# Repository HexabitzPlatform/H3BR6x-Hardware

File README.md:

# H3BR6x-Hardware
Hexabitz 6-Digit 7-Segment Display Module Hardware Design

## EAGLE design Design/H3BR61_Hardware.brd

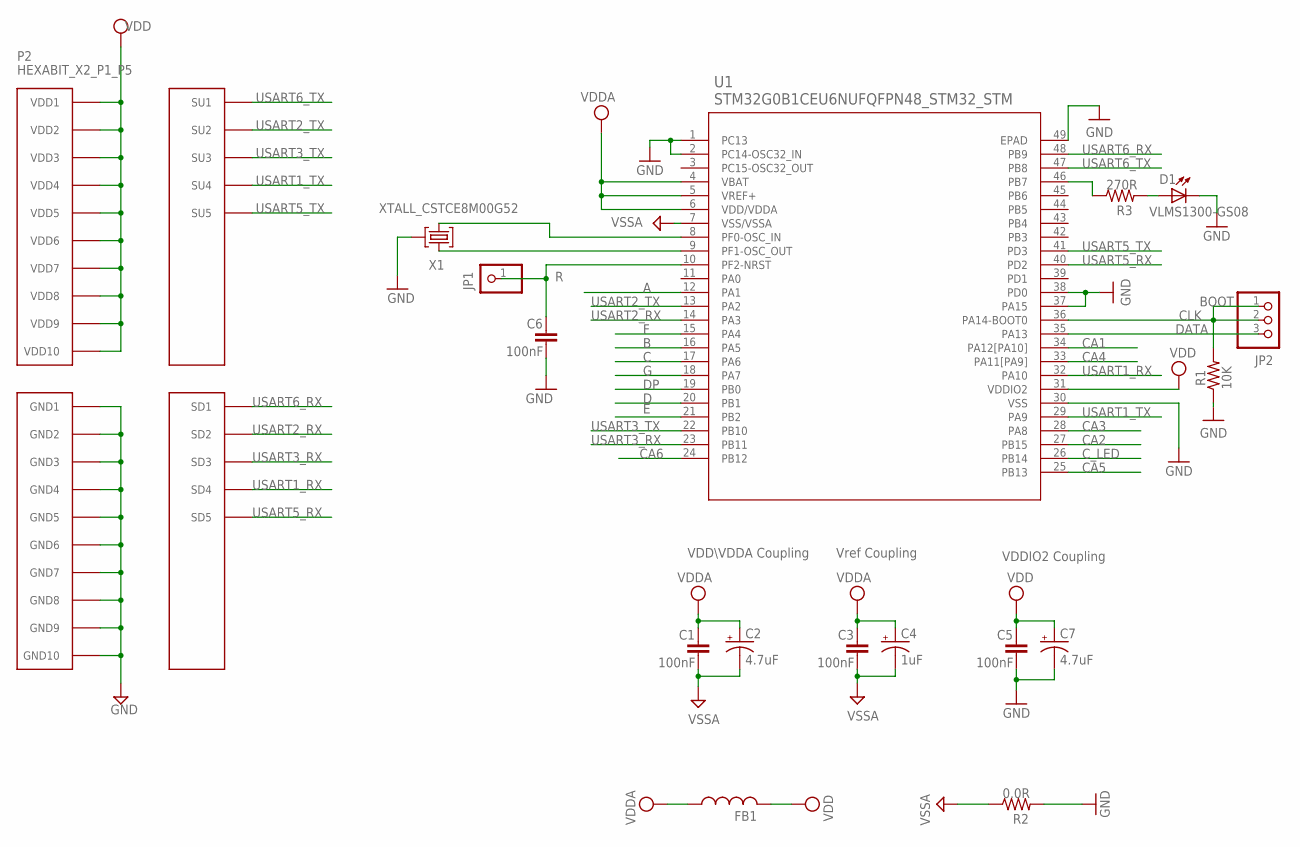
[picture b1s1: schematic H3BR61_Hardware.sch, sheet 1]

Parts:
C1, C3, C5, C6: 100nF; C-0603
C2, C7: 4.7uF; C-0805-POL
C4: 1uF; C-0805-POL
D1: VLMS1300-GS08; MPN VLMS1300-GS08
FB1: FB-0603
JP1: R; 1X01
JP2: PINHD-1X3; 1X03
P2: HEXABIT_X2_P1_P5; HEXABIT_17.32_X2_P1_P5
R1: 10K; R-0603
R2: 0.0R; R-0603
R3: 270R; R-0603
U1: STM32G0B1CEU6NUFQFPN48_STM32_STM; UFQFPN48_STM32_STM
X1: XTALL_CSTCE8M00G52

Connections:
A: U1.12 (PA1); also elsewhere on the board
B: U1.16 (PA5); also elsewhere on the board
C: U1.17 (PA6); also elsewhere on the board
CA1: U1.34 (PA12[PA10]); also elsewhere on the board
CA2: U1.27 (PB15); also elsewhere on the board
CA3: U1.28 (PA8); also elsewhere on the board
CA4: U1.33 (PA11[PA9]); also elsewhere on the board
CA5: U1.25 (PB13); also elsewhere on the board
CA6: U1.24 (PB12); also elsewhere on the board
CLK: JP2.1, JP2.2, R1.2, U1.36 (PA14-BOOT0)
C_LED: U1.26 (PB14); also elsewhere on the board
D: U1.20 (PB1); also elsewhere on the board
DATA: JP2.3, U1.35 (PA13)
DP: U1.19 (PB0); also elsewhere on the board
E: U1.21 (PB2); also elsewhere on the board
F: U1.15 (PA4); also elsewhere on the board
G: U1.18 (PA7); also elsewhere on the board
GND: C5.2, C6.2, C7.2 (-), D1.C, P2.PAD_PD11 (GND1), P2.PAD_PD12 (GND2), P2.PAD_PD13 (GND3), P2.PAD_PD14 (GND4), P2.PAD_PD15 (GND5), P2.PAD_PD16 (GND6), P2.PAD_PD17 (GND7), P2.PAD_PD18 (GND8), P2.PAD_PD19 (GND9), P2.PAD_PD20 (GND10), R1.1, R2.2, U1.1 (PC13), U1.2 (PC14-OSC32_IN), U1.30 (VSS), U1.37 (PA15), U1.38 (PD0), U1.49 (EPAD), X1.P$2 (2); also elsewhere on the board
unnamed: D1.A, R3.2
unnamed: R3.1, U1.46 (PB7)
unnamed: U1.9 (PF1-OSC_OUT), X1.P$1 (1)
unnamed: U1.8 (PF0-OSC_IN), X1.P$3 (3)
unnamed: C6.1, JP1.1, U1.10 (PF2-NRST)
USART1_RX: P2.PAD_PD4 (SD4), U1.32 (PA10)
USART1_TX: P2.PAD_PU4 (SU4), U1.29 (PA9)
USART2_RX: P2.PAD_PD2 (SD2), U1.14 (PA3)
USART2_TX: P2.PAD_PU2 (SU2), U1.13 (PA2)
USART3_RX: P2.PAD_PD3 (SD3), U1.23 (PB11)
USART3_TX: P2.PAD_PU3 (SU3), U1.22 (PB10)
USART5_RX: P2.PAD_PD5 (SD5), U1.40 (PD2)
USART5_TX: P2.PAD_PU5 (SU5), U1.41 (PD3)
USART6_RX: P2.PAD_PD1 (SD1), U1.48 (PB9)
USART6_TX: P2.PAD_PU1 (SU1), U1.47 (PB8)
VDD: C5.1, C7.1 (+), FB1.2, P2.PAD_PU11 (VDD1), P2.PAD_PU12 (VDD2), P2.PAD_PU13 (VDD3), P2.PAD_PU14 (VDD4), P2.PAD_PU15 (VDD5), P2.PAD_PU16 (VDD6), P2.PAD_PU17 (VDD7), P2.PAD_PU18 (VDD8), P2.PAD_PU19 (VDD9), P2.PAD_PU20 (VDD10), U1.31 (VDDIO2); also elsewhere on the board
VDDA: C1.1, C2.1 (+), C3.1, C4.1 (+), FB1.1, U1.4 (VBAT), U1.5 (VREF+), U1.6 (VDD/VDDA)
VSSA: C1.2, C2.2 (-), C3.2, C4.2 (-), R2.1, U1.7 (VSS/VSSA)

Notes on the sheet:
Vref Coupling
VDDIO2 Coupling
VDD\VDDA Coupling
BOOT

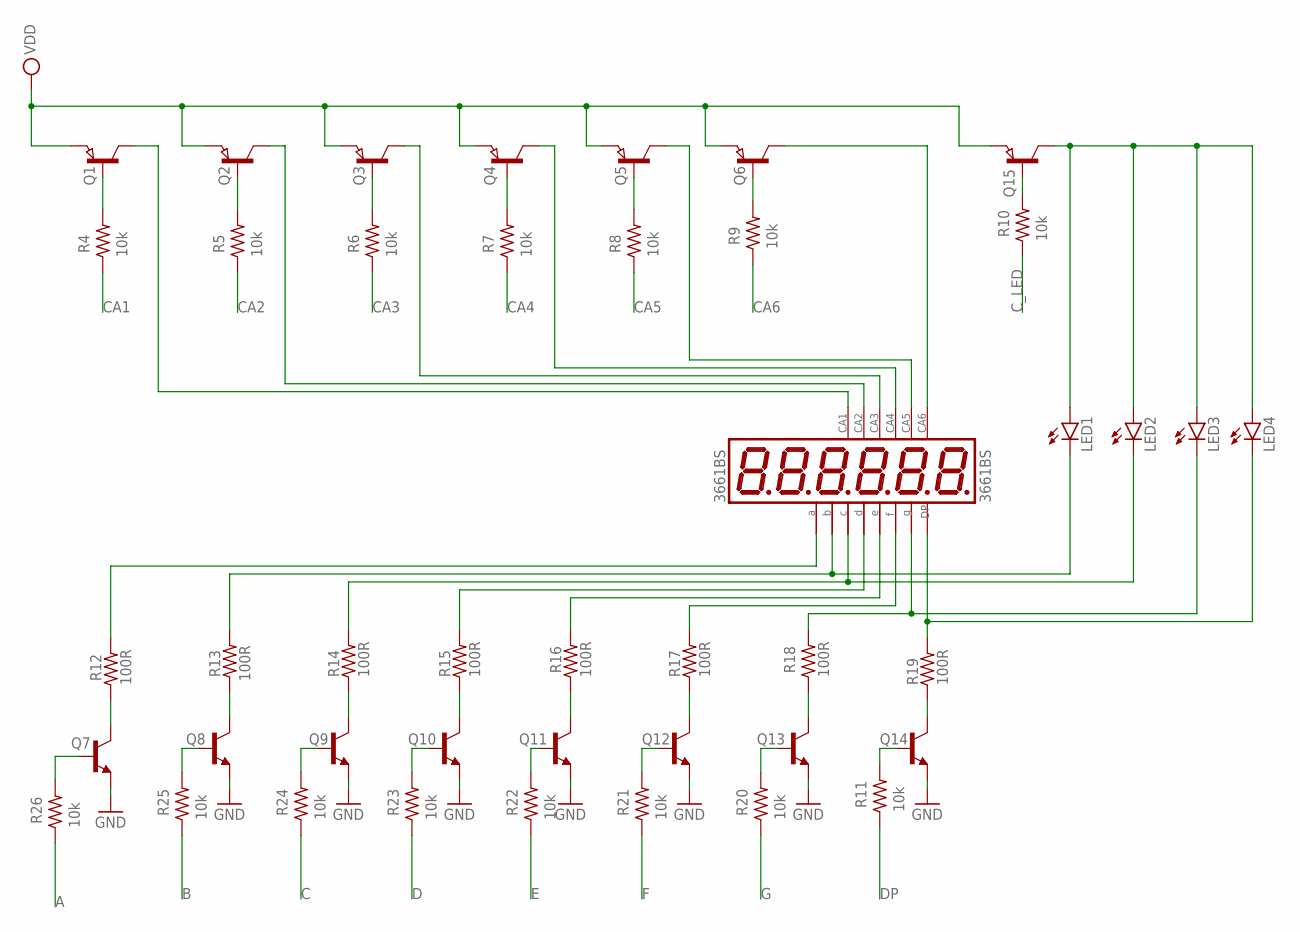
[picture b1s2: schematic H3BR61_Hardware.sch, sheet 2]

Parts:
3661BS: 3661BS
LED1, LED2, LED3, LED4: LED3MM
Q1, Q2, Q3, Q4, Q5, Q6, Q15: SEMICON-SMD-IPC_PNP-TRANSISTOR_SOT23; SEMICON-SMD-IPC_SOT23
Q7, Q8, Q9, Q10, Q11, Q12, Q13, Q14: MMBT3904LT1
R4, R5, R6, R7, R8, R9, R10, R11, R20, R21, R22, R23, R24, R25, R26: 10k; R-0603
R12, R13, R14, R15, R16, R17, R18, R19: 100R; R-0603

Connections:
A: R26.1; also elsewhere on the board
B: R25.1; also elsewhere on the board
C: R24.1; also elsewhere on the board
CA1: R4.1; also elsewhere on the board
CA2: R5.1; also elsewhere on the board
CA3: R6.1; also elsewhere on the board
CA4: R7.1; also elsewhere on the board
CA5: R8.1; also elsewhere on the board
CA6: R9.1; also elsewhere on the board
C_LED: R10.1; also elsewhere on the board
D: R23.1; also elsewhere on the board
DP: R11.1; also elsewhere on the board
E: R22.1; also elsewhere on the board
F: R21.1; also elsewhere on the board
G: R20.1; also elsewhere on the board
GND: Q7.2 (E), Q8.2 (E), Q9.2 (E), Q10.2 (E), Q11.2 (E), Q12.2 (E), Q13.2 (E), Q14.2 (E); also elsewhere on the board
unnamed: Q7.1 (B), R26.2
unnamed: Q8.1 (B), R25.2
unnamed: Q9.1 (B), R24.2
unnamed: Q10.1 (B), R23.2
unnamed: Q11.1 (B), R22.2
unnamed: Q12.1 (B), R21.2
unnamed: Q13.1 (B), R20.2
unnamed: Q14.1 (B), R11.2
unnamed: Q7.3 (C), R12.1
unnamed: Q8.3 (C), R13.1
unnamed: Q9.3 (C), R14.1
unnamed: Q10.3 (C), R15.1
unnamed: Q11.3 (C), R16.1
unnamed: Q12.3 (C), R17.1
unnamed: Q13.3 (C), R18.1
unnamed: Q14.3 (C), R19.1
unnamed: Q1.1 (B), R4.2
unnamed: Q2.1 (B), R5.2
unnamed: Q3.1 (B), R6.2
unnamed: Q4.1 (B), R7.2
unnamed: Q5.1 (B), R8.2
unnamed: Q6.1 (B), R9.2
unnamed: 3661BS.3 (DP), LED4.K (C), R19.2
unnamed: 3661BS.5 (G), LED3.K (C), R18.2
unnamed: 3661BS.12 (F), R17.2
unnamed: 3661BS.1 (E), R16.2
unnamed: 3661BS.2 (D), R15.2
unnamed: 3661BS.4 (C), LED2.K (C), R14.2
unnamed: 3661BS.9 (B), LED1.K (C), R13.2
unnamed: 3661BS.13 (A), R12.2
unnamed: 3661BS.7 (CA), Q6.3 (C)
unnamed: 3661BS.6 (CA), Q5.3 (C)
unnamed: 3661BS.8 (CA), Q4.3 (C)
unnamed: 3661BS.10 (CA), Q3.3 (C)
unnamed: 3661BS.11 (CA), Q2.3 (C)
unnamed: 3661BS.14 (CA), Q1.3 (C)
unnamed: Q15.1 (B), R10.2
unnamed: LED1.A, LED2.A, LED3.A, LED4.A, Q15.3 (C)
VDD: Q1.2 (E), Q2.2 (E), Q3.2 (E), Q4.2 (E), Q5.2 (E), Q6.2 (E), Q15.2 (E); also elsewhere on the board

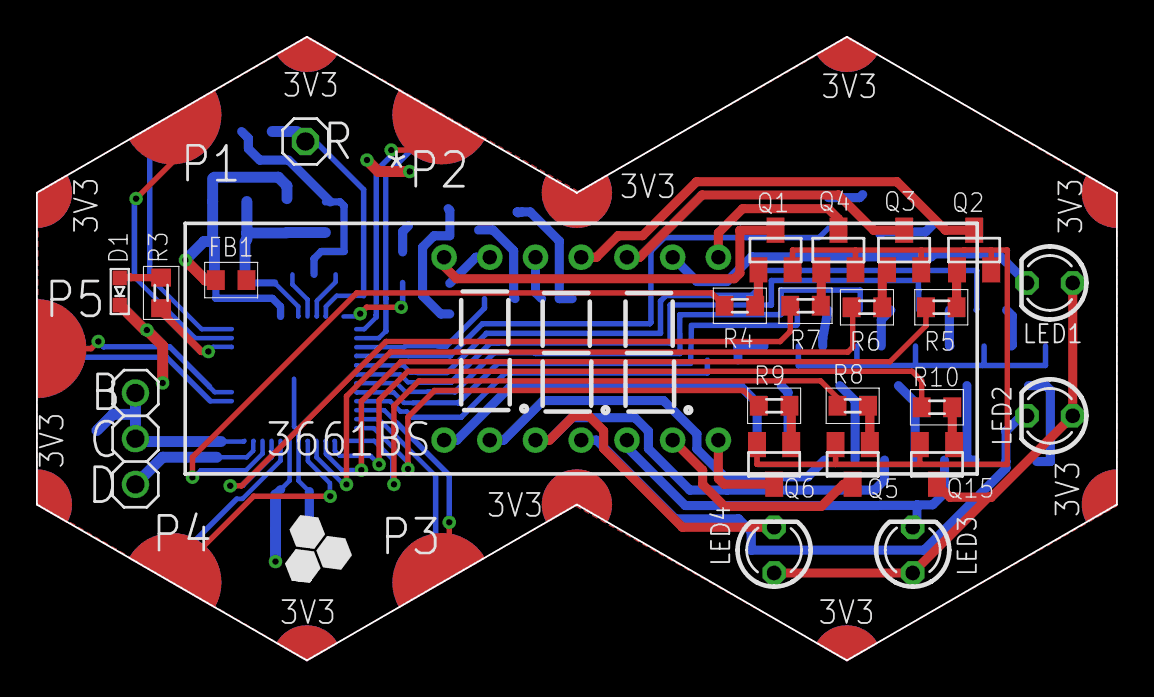
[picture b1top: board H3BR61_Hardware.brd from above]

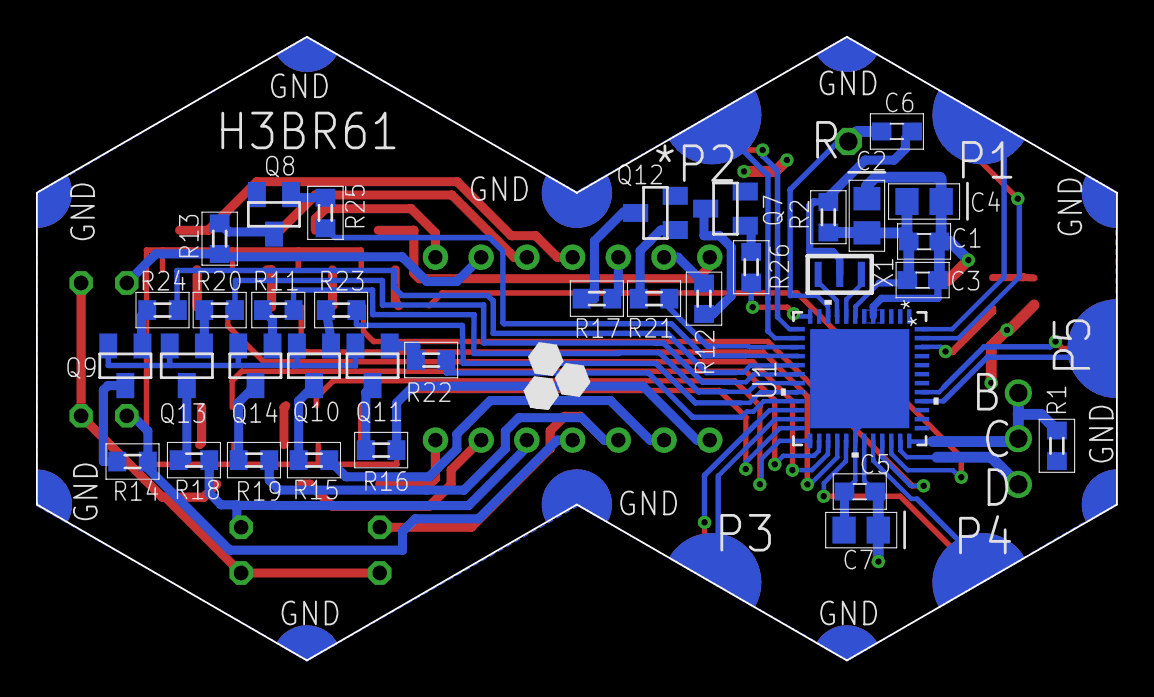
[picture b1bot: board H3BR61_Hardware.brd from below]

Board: 2 copper layers, 60.0 x 34.6 mm, 60 parts (35 on the bottom side), 74 nets.

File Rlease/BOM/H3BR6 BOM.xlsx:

Qty | Value | Designator | Description | MFN | MPN | OCTOPART_URL
4 | LED3mm RED | LED1, LED2, LED3, LED4 | LED 3mm RED Collor | Vishay | TLHK4600 | https://octopart.com/tlhk4600-vishay-39410044?r=sp
1 | PINHD-1X1 | JP1 | PCB Header, Unshrouded, Thru 02 Straight Header, .101, AMPMODU Mod II Series | TE Connectivity | 87227-1 | https://octopart.com/87227-1-te+connectivity-39512052?r=sp
1 | PINHD-1X3 | JP2 | Conn Unshrouded Header HDR 3 POS 2.54mm Solder ST Top Entry Thru-Hole Carton | TE Connectivity | 5-146281-3 | https://octopart.com/5-146281-3-te+connectivity+%2F+amp-3974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
4 | 100nF | C1, C3, C5, C6 | CAP CER 10% X7R 0603 | KEMET | C0603C104K8RACTU | https://octopart.com/c0603c104k8ractu-kemet-145075?r=sp&s=9b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
1 | 1.00uF | C4 | CAP CER 1UF 16V X7R 0805 | YAGEO [VA] | CC0805KKX7R7BB105 | https://octopart.com/cc0805kkx7r7bb105-yageo-8376555?r=sp
2 | 4.7uF | C2, C7 | CAP TANT 4.7UF 10V 20% 0805 | Panasonic | 10TPU4R7MSI | https://octopart.com/10tpu4r7msi-panasonic-29487748?r=sp
1 | 0.0R | R2 | RES SMD 0.0OHM JUMPER 1/10W 0603 | YAGEO [VR] | RC0603JR-070RL | https://octopart.com/rc0603jr-070rl-yageo-1241539?r=sp
8 | 100R | R12, R13, R14, R15, R16, R17, R18, R19 | Thick Film Resistors - SMD 0603 | Yageo | RC0603FR-07100RL | https://octopart.com/rc0603fr-07100rl-yageo-55402879?r=sp
1 | 270.0R | R3 | Thick Film Resistors - SMD 0603 270ohms 5% Tol | Panasonic | ERJ-3GEYJ271V | https://octopart.com/erj-3geyj271v-panasonic-55560546?r=sp
16 | 10K | R1 ,R4, R5, R6, R7, R8, R9, R10, R11, R20, R21, R22, R23, R24, R25, R26 | RES 10 K OHM 5% 0603 | Vishay | CRCW060310K0JNEB | https://octopart.com/crcw060310k0jneb-vishay-46603269
1 | Display 6 DIG | 3661BS | 0.36 inch 6digits RED 8 segment led display Common Anode |  | 3661BS | https://www.aliexpress.com/item/1326420858.html
1 | FB-TDK_MMZ1608Y300B | FB1 | Ind chip Bead Multi-Layer 30 ohms 25% 100MHZ Ferrite 1,5A 0603Punched paper T/R | TDK | MMZ1608Y300BTA00 | https://octopart.com/mmz1608y300bta00-tdk-7906990?r=sp
7 | MMBT3906LT1 | Q1, Q2, Q3, Q4, Q5, Q6, Q15 | Trans GP BJT PNP 40V 0.2A 330mW Automotive 3-Pin SOT-23 T/R | Infineon | MMBT3906LT1HTSA1 | https://octopart.com/mmbt3906lt1htsa1-infineon-21387160?r=sp
8 | MMBT3904LT1 | Q7, Q8, Q9, Q10, Q11, Q12, Q13, Q14 | Transistor, Bipolar, Si, NPN, General Purpose, VCEO 40VDC, IC 200mA, PD 225mW, 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 | ON Semiconductor | MMBT3904LT1G | https://octopart.com/mmbt3904lt1g-on+semiconductor-3280?r=sp
1 | STM32G0B1CEU6N | U1 | MCU 32-Bit ARM Cortex-M0+ RISC 512kByte Flash 1.7V to 3.6V 48-Pin UFQFPN Tray | STMicroelectronics | STM32G0B1CEU6N | https://octopart.com/stm32g0b1ceu6n-stmicroelectronics-11636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
1 | RED | D1 | Red 0603 130آ° Clear 54 mcd 2 V Surface Mount ChipLED ; | Vishay | VLMS1300-GS08 | https://octopart.com/vlms1300-gs08-vishay-21709201?r=sp&s=0n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
1 | XTALL_CSTCE8M00G52 | X1 | 8,0000MHZ 33pF SMD MURATA Resonators | Murata | CSTNE8M00G550000R0 | https://octopart.com/cstne8m00g550000r0-murata-91406934?r=sp

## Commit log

2020-11-28 Finishing PCB
2020-11-28 Fix Wire Width
2020-11-29 Final Design REV 1
2020-12-02 Relase REV 1
2021-04-20 Release REV0
2021-04-21 FIX Rev0
2021-04-22 - Updated BOM..
2022-04-30 -Changing the MC with STM32G0
2022-08-14 Change the License date
2022-08-23 Correcting the Revision number
2023-02-15 -Correcting some documentaion issues

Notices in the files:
parts and their libraries:
COPYRIGHT: Copyright (C) 2022 Ultra Librarian. All rights reserved.
